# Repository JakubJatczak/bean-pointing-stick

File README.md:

## KiCad conversion fork

The whole purpose of the intended changes is to convert hardware production files to KiCad and to generate production files that will allow for manufacturing PCBA using JLCPCB services.
Until this file says otherwise - it's all untested.

Visit [Ploopy website] for an best quality and experience.

I claim no ownership of this design. It is Ploopy’s work, converted to KiCad and shared under CERN-OHL-S-2.0.
# The Ploopy Bean Pointing Stick Mouse

By some stroke of luck, you've made your way here. The Ploopy Bean. Your life will never be the same.

This repository contains all of the design and production files necessary to make a Ploopy Bean. We've also included some kick-ass documentation on how to get it made, assemble it, and program it [which you can find here](https://ploopyco.github.io/bean-pointing-stick/).

What are you waiting for? Your new life awaits.

## QMK?!

Beans bought from the [Ploopy store](https://ploopy.co/shop/bean-pointing-stick/) come with QMK preloaded. [Check out the documentation](https://ploopyco.github.io/bean-pointing-stick/) for instructions on how to load new firmware onto your device. (It's super easy!)

The firmware file that ships with all Beans is included in this repository as well, as `firmwares/bean.uf2`.

In case you are new to the world of QMK, it is an open-source firmware for computer input peripherals. You can find the source code for all of our firmwares in [QMK's Github repository](https://github.com/qmk/qmk_firmware/tree/master/keyboards/ploopyco).

Note that you may have to look for specific development branches in order to find the source for all of our firmwares, as we frequently have pending pull requests.

## Under what license is this released?

As per QMK's licensing requirements, the firmware for the Ploopy Bean Pointing Stick is released under GPLv3. Hardware design files, including electronics and mechanical files, are released under OHL CERN v2-S. Check the respective directories for full license text.

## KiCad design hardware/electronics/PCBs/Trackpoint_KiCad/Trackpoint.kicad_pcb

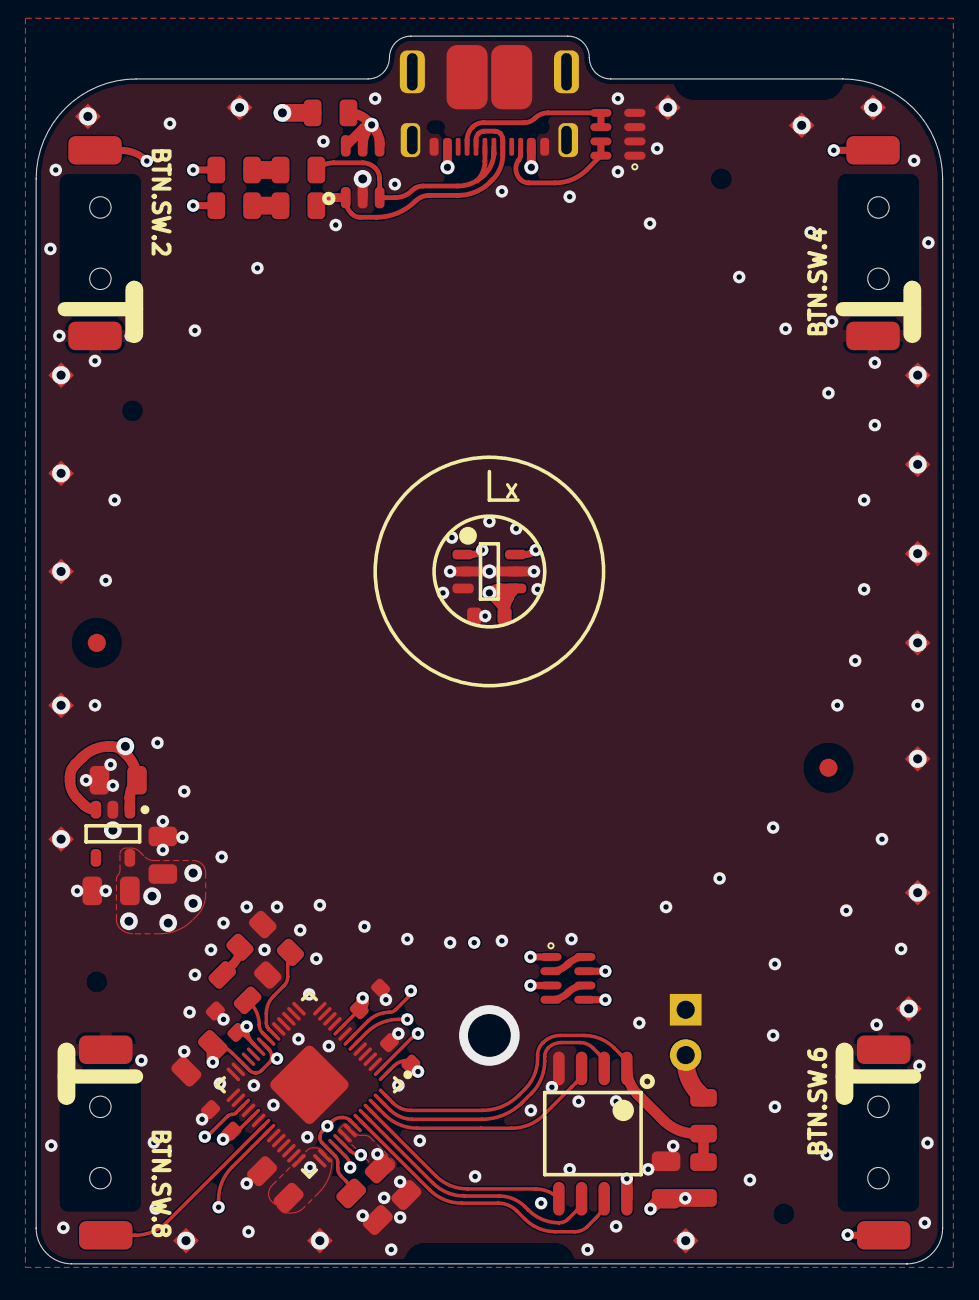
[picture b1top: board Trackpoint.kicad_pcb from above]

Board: 4 copper layers, 50.8 x 68.8 mm, 62 parts (0 on the bottom side), 31 nets.

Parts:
BTN.SW.2, BTN.SW.4, BTN.SW.6, BTN.SW.8: D2LS-21
MCH.FID.1, MCH.FID.2: IPC-7351 Fiducial 1mm; FIDUCIAL_1.5
MCH.FID.3, MCH.FID.4, MCH.FID.5, MCH.FID.6: 1mm Fiducial for OpenPNP; FIDUCIAL-NEW
MCH.LOGO.2: Coordinate system marker for assembly; Coordinate System
MCH.SP.1, MCH.SP.2, MCH.SP.3, MCH.SP.4, MCH.SP.5, MCH.SP.6, MCH.SP.7, MCH.SP.8, MCH.SP.9, MCH.SP.10, MCH.SP.11, MCH.SP.12, MCH.SP.13, MCH.SP.14, MCH.SP.15, MCH.SP.16, MCH.SP.17, MCH.SP.18, MCH.SP.19, MCH.SP.20: Spark Gap; SparkGap
MCU.C.1, MCU.C.2, MCU.C.5, MCU.C.7, MCU.C.21: 0805 X5R; 0805 - TALL
MCU.C.3, MCU.C.4, MCU.C.6, MCU.C.22: 0603 X5R; 0603 capacitor - CAPC1608X06N
MCU.J.1: HEADER2; 2x1
MCU.R.1, MCU.R.2, MCU.R.11: 0805
MCU.U.1: W25Q16JVSSIQ; W25Q128JVS - SOIC127P790X216-8M
MCU.U.5: RP2040; RP2040 - QFN40P700X700X90_HS-57M
MCU.Y.1: RH100-12.000-16-3030
REG.C.12, REG.C.13, REG.C.14: 0805 X5R; 0805 - TALL
REG.U.3: AP2202K-3.3; AP2202 - SOT95P270X145-5N
RSN.C.9: 0603 X5R; 0603 capacitor - CAPC1608X06N
RSN.Ra.2: 1206 Quad; 4x 1k 1% - CAC-80P320X160-8M
RSN.U.6: TMAG5273; TMAG5273 - SOT95P280X145-6M
USB.FB.1, USB.FB.2, USB.FB.3: ACML-0805-601-T; 0805
USB.J.3: DX07S016JA1R1500
USB.R.6, USB.R.7: 0805
USB.Ra.1: 1206 Quad; 4x 10k 1% - CAC-80P320X160-8M
USB.Z.1: IP4220CZ6,125; PESD3V3S4UD - SOT95P275X110-6N

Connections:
1V1: MCU.C.21.2, MCU.C.22.2, MCU.U.5.23, MCU.U.5.45, MCU.U.5.50
3V3: MCU.C.1.2, MCU.C.2.2, MCU.C.3.2, MCU.C.4.2, MCU.C.5.2, MCU.C.6.2, MCU.C.7.2, MCU.R.2.1, MCU.U.1.8, MCU.U.5.1, MCU.U.5.10, MCU.U.5.22, MCU.U.5.26, MCU.U.5.33, MCU.U.5.42, MCU.U.5.43, MCU.U.5.44, MCU.U.5.48, MCU.U.5.49, REG.C.13.2, REG.C.14.2, REG.U.3.5, RSN.C.9.2, RSN.Ra.2.5, RSN.Ra.2.7, RSN.U.6.4
GND: BTN.SW.2.A, BTN.SW.4.A, BTN.SW.6.A, BTN.SW.8.A, MCH.SP.1.1, MCH.SP.2.1, MCH.SP.3.1, MCH.SP.4.1, MCH.SP.5.1, MCH.SP.6.1, MCH.SP.7.1, MCH.SP.8.1, MCH.SP.9.1, MCH.SP.10.1, MCH.SP.11.1, MCH.SP.12.1, MCH.SP.13.1, MCH.SP.14.1, MCH.SP.15.1, MCH.SP.16.1, MCH.SP.17.1, MCH.SP.18.1, MCH.SP.19.1, MCH.SP.20.1, MCU.C.1.1, MCU.C.2.1, MCU.C.3.1, MCU.C.4.1, MCU.C.5.1, MCU.C.6.1, MCU.C.7.1, MCU.C.21.1, MCU.C.22.1, MCU.J.1.1, MCU.U.1.4, MCU.U.5.3, MCU.U.5.4, MCU.U.5.5, MCU.U.5.6, MCU.U.5.9, MCU.U.5.11, MCU.U.5.12, MCU.U.5.13, MCU.U.5.14, MCU.U.5.15, MCU.U.5.16, MCU.U.5.17, MCU.U.5.18, MCU.U.5.19, MCU.U.5.27, MCU.U.5.28, MCU.U.5.29, MCU.U.5.30, MCU.U.5.32, MCU.U.5.34, MCU.U.5.37, MCU.U.5.38, MCU.U.5.39, MCU.U.5.40, MCU.U.5.41, MCU.U.5.57, MCU.Y.1.2, MCU.Y.1.4, REG.C.12.1, REG.C.13.1, REG.C.14.1, REG.U.3.2, RSN.C.9.1, RSN.U.6.2, RSN.U.6.3, RSN.U.6.5, USB.J.3.1, USB.J.3.12, USB.J.3.SHELL, USB.Ra.1.1, USB.Ra.1.2, USB.Ra.1.3, USB.Ra.1.4, USB.Z.1.2
NetBTN.SW.2_B: BTN.SW.2.B, MCU.U.5.31
NetBTN.SW.4_B: BTN.SW.4.B, MCU.U.5.8
NetBTN.SW.6_B: BTN.SW.6.B, MCU.U.5.36
NetBTN.SW.8_B: BTN.SW.8.B, MCU.U.5.35
NetMCU.J.1_2: MCU.J.1.2, MCU.R.1.1
NetMCU.R.1_2: MCU.R.1.2, MCU.R.2.2, MCU.U.1.1, MCU.U.5.56
NetMCU.R.11_1: MCU.R.11.1, MCU.U.5.21
NetMCU.R.11_2: MCU.R.11.2, MCU.Y.1.3
NetMCU.U.1_2: MCU.U.1.2, MCU.U.5.55
NetMCU.U.1_3: MCU.U.1.3, MCU.U.5.54
NetMCU.U.1_5: MCU.U.1.5, MCU.U.5.53
NetMCU.U.1_6: MCU.U.1.6, MCU.U.5.52
NetMCU.U.1_7: MCU.U.1.7, MCU.U.5.51
NetMCU.U.5_2: MCU.U.5.2, RSN.Ra.2.3, RSN.U.6.6
NetMCU.U.5_7: MCU.U.5.7, RSN.Ra.2.1, RSN.U.6.1
NetMCU.U.5_20: MCU.U.5.20, MCU.Y.1.1
NetMCU.U.5_46: MCU.U.5.46, USB.R.6.2
NetMCU.U.5_47: MCU.U.5.47, USB.R.7.2
NetREG.C.12_2: REG.C.12.2, REG.U.3.1, REG.U.3.3, USB.FB.1.2
NetRSN.Ra.2_2: RSN.Ra.2.2, RSN.Ra.2.8
NetRSN.Ra.2_4: RSN.Ra.2.4, RSN.Ra.2.6
NetUSB.FB.1_1: USB.FB.1.1, USB.J.3.2, USB.J.3.11, USB.Z.1.4, USB.Z.1.5, USB.Z.1.6
NetUSB.FB.2_1: USB.FB.2.1, USB.J.3.5, USB.J.3.8, USB.Z.1.1
NetUSB.FB.2_2: USB.FB.2.2, USB.R.6.1
NetUSB.FB.3_1: USB.FB.3.1, USB.J.3.6, USB.J.3.7, USB.Z.1.3
NetUSB.FB.3_2: USB.FB.3.2, USB.R.7.1
NetUSB.J.3_3: USB.J.3.3, USB.Ra.1.7, USB.Ra.1.8
NetUSB.J.3_9: USB.J.3.9, USB.Ra.1.5, USB.Ra.1.6

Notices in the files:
hardware/electronics/PCBs/Trackpoint_KiCad/Trackpoint.kicad_pcb:
Licensed under the
CERN-OHL-S v2
Copyright Ploopy
